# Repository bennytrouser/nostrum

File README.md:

# Nostrum
A 32 key ergo split keyboard with minimal splay.
- 3° Splay on pinky and ring columns
- Inspiration from the [Hummingbird](https://github.com/PJE66/hummingbird) style [Berylline](https://github.com/jcmkk3/trochilidae#berylline) by [jcmkk3](https://github.com/jcmkk3)
- Created with the wonderful [ergogen](https://github.com/ergogen/ergogen) and KiCad7. Case files created with Autodesk Fusion360.

## PCB
| Top  | Bottom |
| ------------- | ------------- |
|   |  |

## Base Alpha Keymap
ColemakDH Based

## Notes
- The reset and power switch can be mounted on either side. I think it works better with the case/bottom plate. 
- There is a hole on the base of the case to use a paper clip to activate the manual reset if mounted on the underside.
- The "feet" on the base are made from 1mm silicone rubber sheet as I prefer this to the standard bumpons.

## Warning
The original case was experimental. As such I have removed the files for the top part of the case and updated the bottom part that works great as a minimal bottom "tray". I have updated the STLs and pcb to avoid weakness on the mounting and to fix an issue with hotswaps causing fitment issues but I have not done a test print.

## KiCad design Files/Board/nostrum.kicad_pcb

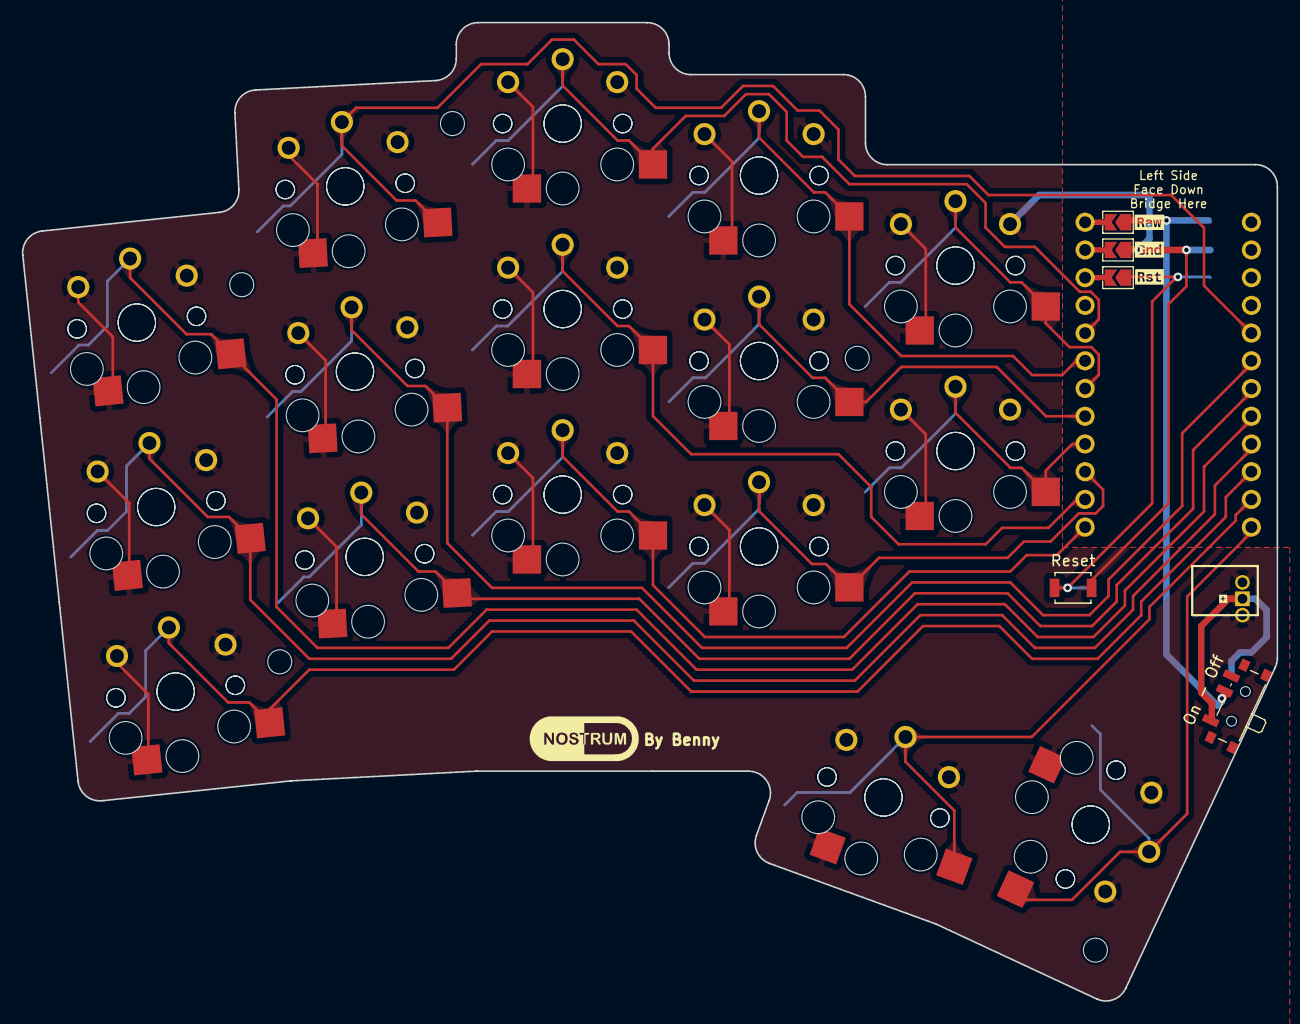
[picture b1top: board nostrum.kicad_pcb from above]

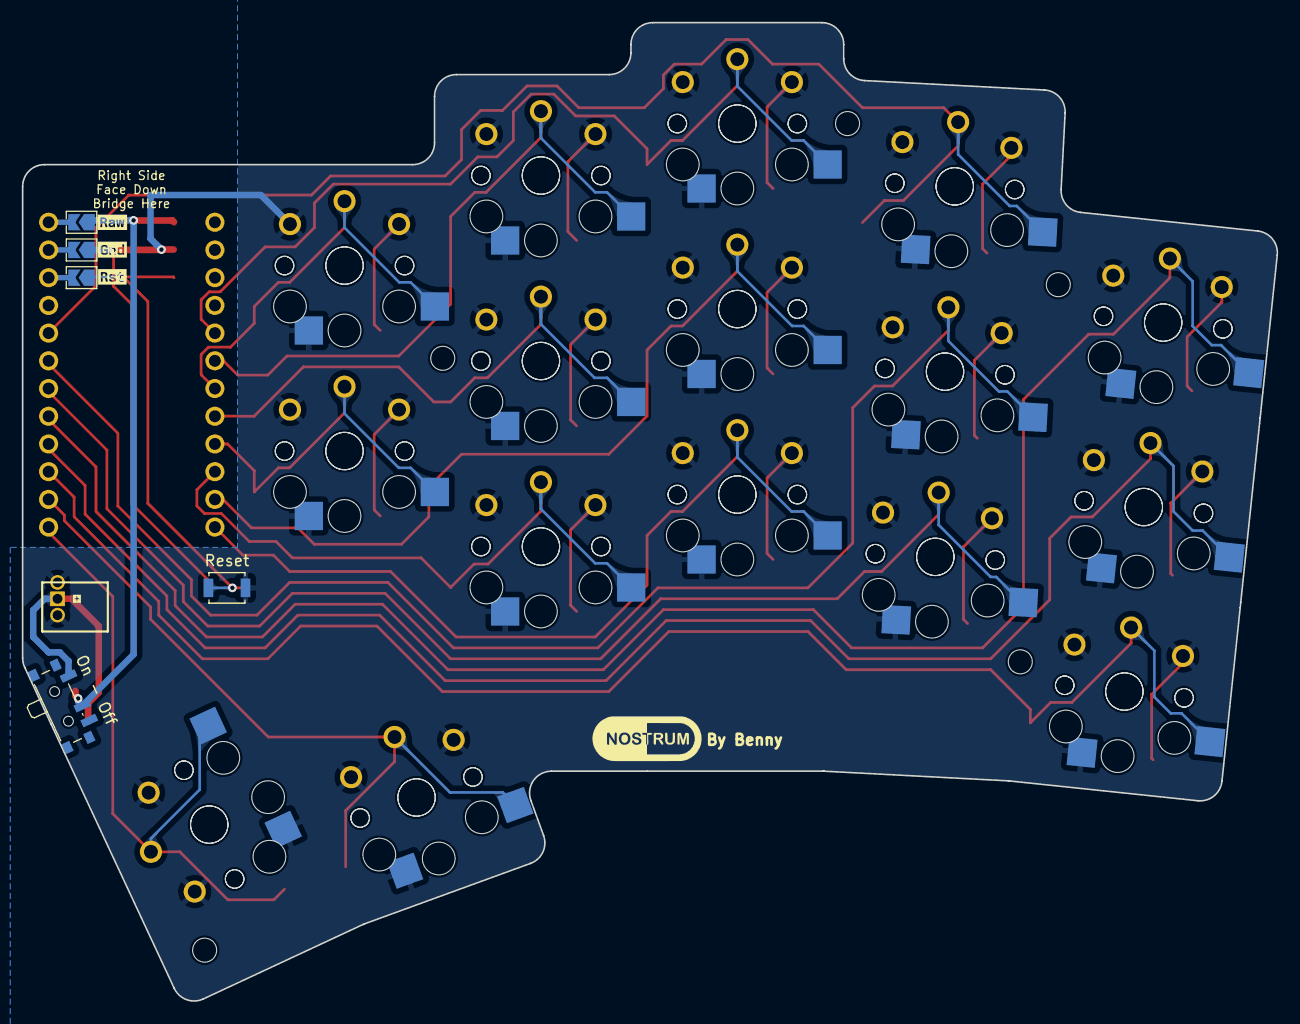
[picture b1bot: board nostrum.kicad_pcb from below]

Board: 2 copper layers, 115.0 x 89.7 mm, 43 parts (4 on the bottom side), 19 nets.

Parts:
MCU1: ProMicroSimpleJumper
On - Off: SW_SPDT_PCM12
Reset: SW_SPST_B3U-1000P
S1, S2, S3, S4, S5, S6, S7, S8, S9, S10, S11, S12, S13, S14, S15, S16, S17, S18, S19, S20, S21, S22, S23, S24, S25, S26, S27, S28, S29, S30, S31, S32: PG1350
kibuzzard-64BC4B3E: G***; kibuzzard-64BC4B3E
kibuzzard-64BC4B8B: G***; kibuzzard-64BC4B8B
kibuzzard-64BC4B21: G***; kibuzzard-64BC4B21
kibuzzard-64BC4B76: G***; kibuzzard-64BC4B76
kibuzzard-64BC4BA6: G***; kibuzzard-64BC4BA6
kibuzzard-64BC4CE6: G***; kibuzzard-64BC4CE6
kibuzzard-6498B72D, kibuzzard-6498B72D#2: G***; kibuzzard-6498B72D

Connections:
GND: MCU1.2, Reset.2, S1.1, S2.1, S3.1, S4.1, S5.1, S6.1, S7.1, S8.1, S9.1, S10.1, S11.1, S12.1, S13.1, S14.1, S15.1, S16.1, S17.1, S18.1, S19.1, S20.1, S21.1, S22.1, S23.1, S24.1, S25.1, S26.1, S27.1, S28.1, S29.1, S30.1, S31.1, S32.1
RAW: MCU1.1, On - Off.2
RST: MCU1.3, Reset.1
matrix_index_bottom: MCU1.10, S10.2, S26.2
matrix_index_home: MCU1.8, S11.2, S27.2
matrix_index_top: MCU1.6, S12.2, S28.2
matrix_inner_bottom: MCU1.9, S13.2, S29.2
matrix_inner_home: MCU1.7, S14.2, S30.2
matrix_middle_bottom: MCU1.12, S7.2, S23.2
matrix_middle_home: MCU1.11, S8.2, S24.2
matrix_middle_top: MCU1.5, S9.2, S25.2
matrix_pinky_bottom: MCU1.22, S1.2, S17.2
matrix_pinky_home: MCU1.21, S2.2, S18.2
matrix_pinky_top: MCU1.20, S3.2, S19.2
matrix_ring_bottom: MCU1.19, S4.2, S20.2
matrix_ring_home: MCU1.18, S5.2, S21.2
matrix_ring_top: MCU1.17, S6.2, S22.2
thumb_reachy: MCU1.24, S16.2, S32.2
thumb_tucky: MCU1.23, S15.2, S31.2

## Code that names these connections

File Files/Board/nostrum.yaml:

units:
  # capx: 17        # Key cap size horizontal
  # capy: 16        # Key cap size vertical
  capx: 17.5   # Actual mbk size
  capy: 16.5   # Actual mbk size
  thumbcapx: 26.5 # Actual mbk 1.5u length
  kx: cx + 0.5    # Key spacing horizontal
  ky: cy + 0.5    # Key spacing vertical
  pinky_splay: 3  # Degrees of splay between pinky and ring columns
  pinky_adj: -10   # Adjustment to compensate for splay spacing
  ring_splay: 3
  ring_adj: -8
  middle_splay: 0
  middle_adj: 0
  thumb_offsetx: 0.25kx
  promicro_x: 33
  promicro_y: 18
  outx: 0.5capx +1  # Used for plate outlines
  outy: 0.5capy +1  # Used for plate outlines

points:
  zones.matrix:
    anchor:
      rotate: ring_splay + pinky_splay
    key:
      width: capx
      height: capy
      spread: cx      
      padding: cy
      autobind: false
    rows:
      bottom.bind: [1, 1, 1, 1]
      home.bind: [1, 1.5, 0, 1]
      top.bind: [1, 2, 0, 1]
    columns:
      pinky:
        rows:
          bottom.bind: [1, 1, 1, 1]
          home.bind: [1, 1.5, 0, 1]
          top.bind: [1, 2, 0, 1]
      ring:
        key:
          stagger: 0.55U
          splay: -pinky_splay
          origin: [0, pinky_adj]
        rows:
          bottom.bind: [1,1.5,11.9,0]
          home.bind: [1,1.5,0,1]
          top.bind: [1,2,1,1]
      middle:
        key:
          stagger: 0.25U
          splay: -ring_splay
          origin: [0, ring_adj]
        rows:
          bottom.bind: [1,1,17.1,0]
          home.bind: [1,1,0,1]
          top.bind: [1,1,0,1]
      index:
        key.stagger: -0.25U
        rows:
          bottom.bind: [1,1,12.341,1]
          home.bind: [1,1,0,1]
          top.bind: [1,1,0,1]
      inner:
        key.stagger: 0.5ky
        rows:
          top.skip: true
          bottom.bind: [1,2,22.590471307,1]
          home.bind: [1,2,20,1]
  zones.thumb:
    anchor:
      ref: matrix_index_top
      shift: [0.6u,-57]
      rotate: -20
    key:
      width: capx
      height: capy
      autobind: false
    rows:
      home:
    columns:
      left.key:
        name: thumb_tucky
        bind: [0,3,1,1] # U,R,D,L
      right.key:
        spread: kx+0.2
        stagger: 0.225kx
        rotate: -95
        name: thumb_reachy
        bind: [1,1,2,1.2191] # R,D,L,U

  # MCU
  zones.mcu:
    anchor:
      ref: matrix_inner_home
      shift: [19.5,-0.5cx]
      rotate: -90
    key:
      width: promicro_x
      height: promicro_y
      autobind: false
  # Power slider
  zones.pcm12:
    anchor:
      - ref: mcu
        shift: [0.5promicro_x + 12, 0.4promicro_y + 1]
        rotate: 180
    key:
      name: pcm12
      height: 2.6
      width: 6.7
  # Reset switch
  zones.reset:
    anchor:
      - ref: mcu
        shift: [.5promicro_x + 4, -0.5promicro_y + 10]    
    key:
      name: reset
      height: 3
      width: 2.5
  # JST
  zones.bat:
    anchor:
      - ref: mcu
        shift: [0.5promicro_x + 3.5, -0.5promicro_y + 3.25]
        rotate: 90
    key:
      name: bat
      height: 5
      width: 4.5

  # Mounting Holes
  zones.mount_tl:
    anchor:
      - ref: matrix_ring_home
        shift: [-0.5cx -0.95,0.5cy]
    key:
      name: mounthole_tl
      height: 2.2
      width: 2.2
      footprints:
  zones.mount_tr:
    anchor:
      - ref: matrix_inner_bottom
        shift: [-0.5cx,0.5cy]
    key:
      name: mounthole_tr
      height: 2.2
      width: 2.2
  zones.mount_tm:
    anchor:
      - ref: matrix_middle_top
        shift: [-0.5cx -1.1,0]
    key:
      name: mounthole_tm
      height: 2.2
      width: 2.2
  zones.mount_bl:
    anchor:
      - ref: matrix_ring_bottom
        shift: [-0.46cx,-0.6cy+1]
    key:
      name: mounthole_bl
      height: 2.2
      width: 2.2
  zones.mount_br:
    anchor:
      - ref: thumb_reachy
        shift: [0.5 thumbcapx -3,0.5 capy -3]
    key:
      name: mounthole_br
      height: 2.2
      width: 2.2

outlines:
  _casecuts:
    - what: rectangle
      where:
        - /matrix_.*/
        - /thumb_.*/
      size: [ 13.85, 13.85]
      bound: false
  _keycapsbound:
    - what: rectangle
      where:
        - /matrix_.*/
        - /thumb_tucky/
      size: [capx, capy]
      bound: true
    - what: rectangle
      where:
        - /thumb_reachy/
      size: [thumbcapx, 1capy]
      bound: true
  _keycapsunbound:
    - what: rectangle
      where:
        - /matrix_.*/
        - /thumb_tucky/
      size: [capx, capy]
      bound: false
    - what: rectangle
      where:
        - /thumb_reachy/
      size: [thumbcapx, 1capy]
      bound: false
    - what: rectangle
      where:
        - /mcu/
      size: [promicro_x,promicro_y]
      bound: false
  _mcu:
    - what: rectangle
      where: mcu
      size: [promicro_x, promicro_y]
  _mcu_extra:
    - what: polygon
      bound: true
      operation: stack
      points:
        - ref: matrix_inner_home
          shift: [0.5capx, 0.5capy+1]
        - ref: matrix_inner_home
          shift: [29.5, 0.5capy+1]
        - ref: thumb_reachy
          shift: [-16.355,0]
          affect: y
        - ref: thumb_reachy
          orient: -95
          shift: [-0.5capy-1,0]
        - ref: thumb_reachy
          orient: -95
          shift: 10
  _mountholes:
    - what: circle
      where: /mount.*/
      radius: 1.1
  _platecut:
    - ^_keycapsbound
    - _mcu_extra
  plate:
    - name: _platecut
      fillet: 2
  preview:
    - ^plate
    - ^_keycapsunbound
    - ^_mountholes
  case:
    - ^plate
    - ^_casecuts
    - ^_mcu
    - ^_mountholes

pcbs.bennyv2:
  outlines.main:
    outline: plate
  footprints:
    - what: choc
      where:
        - /matrix_.*/
        - /thumb_.*/
      adjust.rotate: 180
      params:
        from: GND
        to: "{{name}}"
        reverse: true
        keycaps: true
        hotswap: true
    - what: choc
      where:
        - /matrix_.*/
        - /thumb_.*/
      params:
        from: GND
        to: "{{name}}"
        reverse: true
        keycaps: true
    - what: promicro
      where:
        ref: mcu
        shift: [1, 0]
      params:
        orientation: down
        P5: matrix_pinky_top
        P2: matrix_ring_top
        P21: matrix_middle_top
        P20: matrix_index_top
        P19: matrix_inner_home
        P6: matrix_pinky_home
        P3: matrix_ring_home
        P16: matrix_middle_home
        P18: matrix_index_home
        P15: matrix_inner_bottom
        P7: matrix_pinky_bottom
        P4: matrix_ring_bottom
        P10: matrix_middle_bottom
        P14: matrix_index_bottom
        P8: thumb_tucky
        P9: thumb_reachy
    - what: jstph
      where:
        ref: bat
      params:
        pos: pos
        neg: GND
    - what: button
      where:
        ref: reset
      adjust.rotate: 90
      params:
        from: RST
        to: GND
    - what: slider
      where:
        ref: pcm12
      params:
        from: pos
        to: RAW
    - what: via
      where:
        - /mount.*/
      params:
        net: ""

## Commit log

2023-07-22 Create LICENSE
2023-07-22 svg upload
2023-07-22 Readme edit
2023-07-23 add pngs
2023-07-23 png replace
2023-07-25 images and readme edit
2023-07-25 edit
2023-07-25 Final Readme edit
2023-07-31 STL and PCB fixes. Readme update
2023-07-31 spelling
2023-07-31 image update
2023-08-01 Image updates
2023-08-23 xiao footprint
